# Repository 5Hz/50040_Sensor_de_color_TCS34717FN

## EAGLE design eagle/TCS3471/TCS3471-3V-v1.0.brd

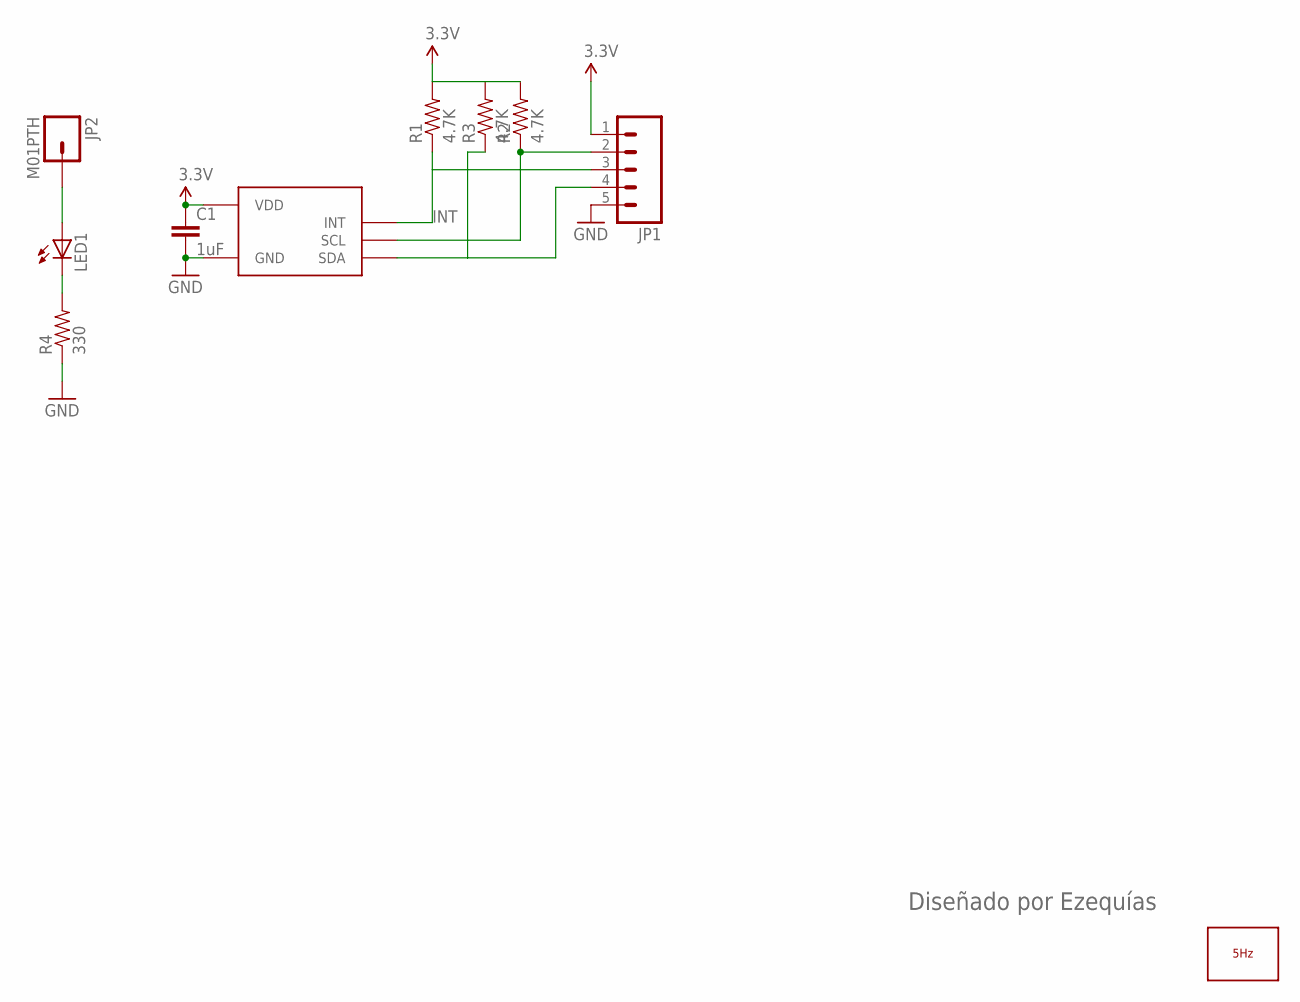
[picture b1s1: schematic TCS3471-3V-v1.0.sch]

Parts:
C1: 1uF; 0603-CAP
JP1: M05PTH; 1X05
JP2: M01PTH; 1X01
LED1: LED0603; LED-0603
LOGO1: LOGO_5HZ_H_5MM; 5HZ_LOGO_H_5MM
R1, R2, R3: 4.7K; 0603-RES
R4: 330; 0603-RES
U$1: TCS3471

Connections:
3.3V: C1.1, JP1.1, R1.2, R2.2, R3.2, U$1.P$1 (VDD)
GND: C1.2, JP1.5, R4.1, U$1.P$3 (GND)
INT: JP1.3, R1.1, U$1.P$5 (INT)
unnamed: LED1.C, R4.2
unnamed: JP2.1, LED1.A
unnamed: JP1.2, R2.1, U$1.P$2 (SCL)
SDA: JP1.4, R3.1, U$1.P$6 (SDA)

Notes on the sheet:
Diseñado por Ezequías

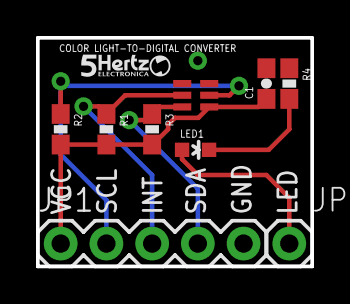
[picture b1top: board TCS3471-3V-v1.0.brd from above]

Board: 2 copper layers, 15.2 x 12.7 mm, 10 parts (0 on the bottom side), 7 nets.

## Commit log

2014-01-10 creación
2014-05-09 Corrección código
2015-03-09 Correccion de ejemplo para sensor de color
    Agregadas funciones que leen registros del sensor para simplificar código

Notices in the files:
parts and their libraries:
SparkFun: Licensing: CC v3.0 Share-Alike You are welcome to use this library for commercial purposes.
